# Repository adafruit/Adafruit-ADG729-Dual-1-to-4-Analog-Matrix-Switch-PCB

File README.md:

## Adafruit ADG729 Dual 1-to-4 Analog Matrix Switch PCB

<a href="http://www.adafruit.com/products/5932"><br/>
Click here to purchase one from the Adafruit shop</a>

PCB files for the Adafruit ADG729 Dual 1-to-4 Analog Matrix Switch. 

Format is EagleCAD schematic and board layout
* https://www.adafruit.com/product/5932

### Description

Analog switches are a solid state alternative to relays, when you want a smaller, lower-power technology that won't wear out mechanically. And, as the name implies, you can use the Adafruit ADG729 Dual 1-to-4 Analog Matrix Switches to connect between two sets of four analog signals, much like 8 mechanical switches. These chips tend to be tiny surface mount parts, so this breakout will let anyone use the ADG729 switch for signals up to 5V, without fiddly soldering.

The ADG729 uses I2C to select which of the 8 channels switches to turn on or off. Four channels connect to the DA analog pin, and the other four channels connect to the DB analog pin. Note that unlike digital switches and multiplexers, these are not 'input' and 'output' because the signal is bidirectional. You could have the DA or DB signal be an input to 4 outputs, or the 4 inputs to one output.

Also, the ADG729 isn't really a 'selecting multiplexer', its a matrix switch with 8 independent switches. That means that yes, you could treat it like an DP4T where you select which signal is routed to the D pin, you can also turn on multiple switches to 'merge' the signals together. If you want all 8 signals to be able to route to a single pin, check out the ADG728.

Unlike a relay or mechanical switch, analog switches don't wear out, and the switch time is near instant, about 100nS. The ADG729 chip also guarantees break-before-make so the deselected switches will open before selected switches close.

However, there's a few things to watch out for:

* The VIN power pin (the red wire if using a STEMMA QT cable) must as high as the highest analog voltages you want to switch. That means if the analog signals are no more than 5VDC, the V+ pin must be higher than 5V. You cannot power this pin with 3.3V and switch 5V signals.
* It cannot switch signals below ground. No negative voltages can be applied to the Switch or DA/DB pins!
* Analog switches are for signals, not power! Since this is not a mechanical switch, the signals pass through circuitry that is not designed to source or sink current. This is great for analog signal voltages, and is not good for providing more than a few mA of current.

In addition to the 8 switch S pins and the two D pins that can be switched to, there's also two I2C address pins so you can change the default address from 0x44 up to 0x47.

To get you going fast, we spun up a custom-made PCB in the STEMMA QT form factor, making it easy to interface with. The STEMMA QT connectors on either side are compatible with the SparkFun Qwiic I2C connectors. This allows you to make solderless connections between your development board and the ADG or to chain it with a wide range of other sensors and accessories using a compatible cable.

### License

Adafruit invests time and resources providing this open source design, please support Adafruit and open-source hardware by purchasing products from [Adafruit](https://www.adafruit.com)!

Designed by Limor Fried/Ladyada for Adafruit Industries.

Creative Commons Attribution/Share-Alike, all text above must be included in any redistribution. 
See license.txt for additional details.

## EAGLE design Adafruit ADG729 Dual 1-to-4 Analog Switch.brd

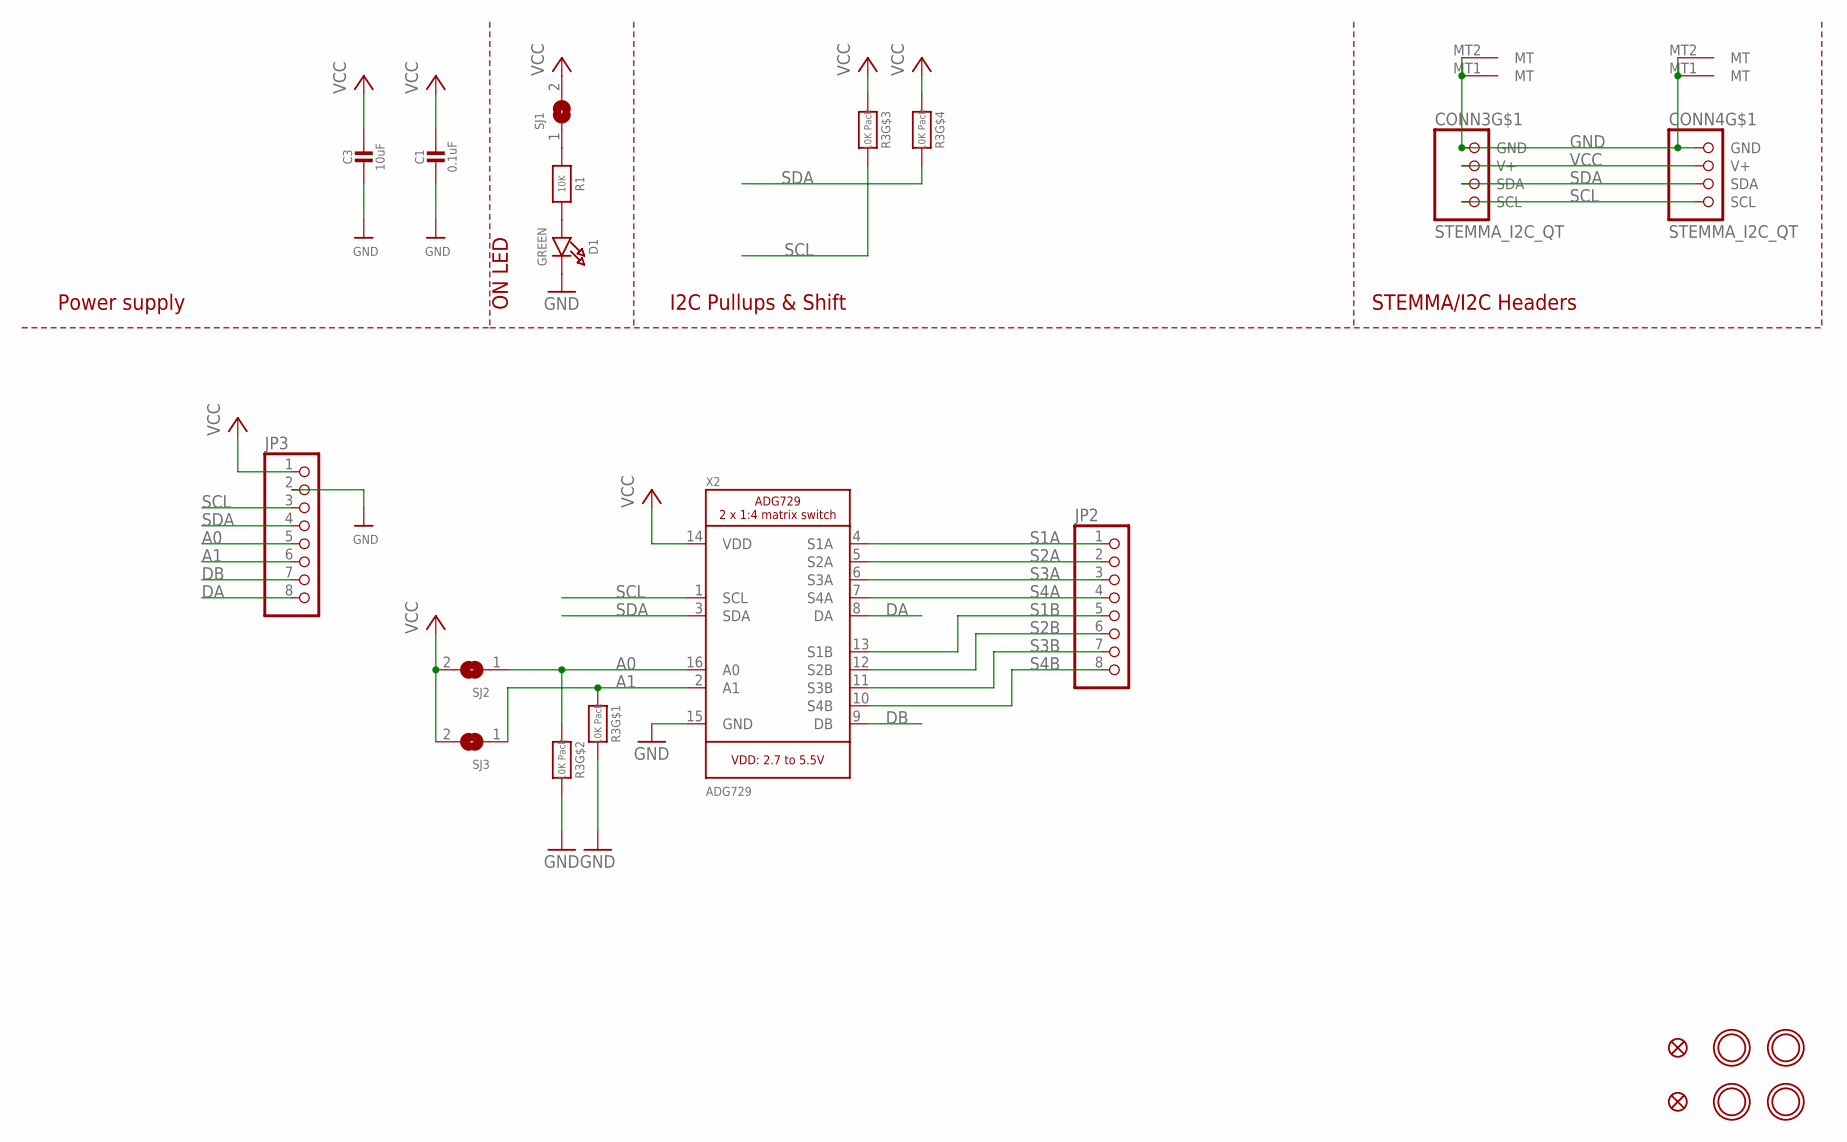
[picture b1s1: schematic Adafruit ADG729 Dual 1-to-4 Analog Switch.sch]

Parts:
C1: 0.1uF; 0603-NO
C3: 10uF; 0805-NO
CONN3, CONN4: STEMMA_I2C_QT; JST_SH4
D1: GREEN; CHIPLED_0603_NOOUTLINE
FID3, FID4: FIDUCIAL_1MM
JP2, JP3: HEADER-1X870MIL; 1X08_ROUND_70
R1: 10K; 0603-NO
R3: 10K Pack; RESPACK_4X0603
SJ1: SOLDERJUMPERCLOSED; SOLDERJUMPER_CLOSEDWIRE
SJ2, SJ3: SOLDERJUMPER; SOLDERJUMPER_ARROW_NOPASTE
U$1, U$17, U$19, U$21: MOUNTINGHOLE2.5; MOUNTINGHOLE_2.5_PLATED
X2: ADG729; TSSOP16

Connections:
A0: JP3.5, R3.2 (1), SJ2.1, X2.16 (A0)
A1: JP3.6, R3.1, SJ3.1, X2.2 (A1)
DA: JP3.8, X2.8 (DA)
DB: JP3.7, X2.9 (DB)
GND: C1.2, C3.2, CONN3.1 (GND), CONN3.MT1 (MT), CONN3.MT2 (MT), CONN4.1 (GND), CONN4.MT1 (MT), CONN4.MT2 (MT), D1.C, JP3.2, R3.7 (2), R3.8 (2), X2.15 (GND)
unnamed: D1.A, R1.2
unnamed: R1.1, SJ1.1
S1A: JP2.1, X2.4 (S1A)
S1B: JP2.5, X2.13 (S1B)
S2A: JP2.2, X2.5 (S2A)
S2B: JP2.6, X2.12 (S2B)
S3A: JP2.3, X2.6 (S3A)
S3B: JP2.7, X2.11 (S3B)
S4A: JP2.4, X2.7 (S4A)
S4B: JP2.8, X2.10 (S4B)
SCL: CONN3.4 (SCL), CONN4.4 (SCL), JP3.3, R3.6 (2), X2.1 (SCL)
SDA: CONN3.3 (SDA), CONN4.3 (SDA), JP3.4, R3.5 (2), X2.3 (SDA)
VCC: C1.1, C3.1, CONN3.2 (V+), CONN4.2 (V+), JP3.1, R3.3 (1), R3.4 (1), SJ1.2, SJ2.2, SJ3.2, X2.14 (VDD)

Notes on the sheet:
I2C Pullups & Shift
STEMMA/I2C Headers
ON LED
Power supply

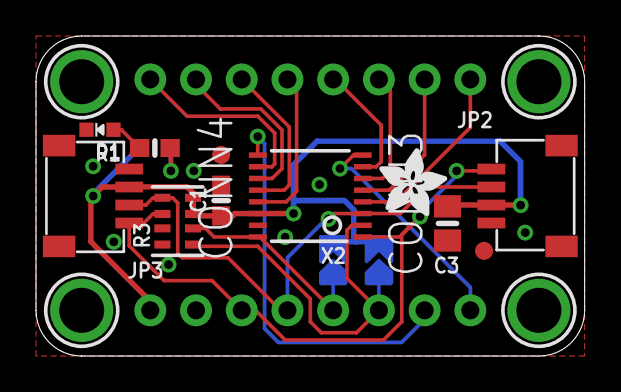
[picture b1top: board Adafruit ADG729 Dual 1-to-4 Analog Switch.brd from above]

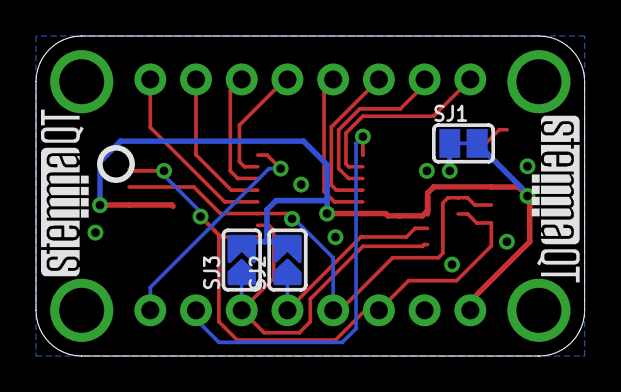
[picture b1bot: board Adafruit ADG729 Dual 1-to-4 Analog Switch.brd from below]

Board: 2 copper layers, 30.5 x 17.8 mm, 47 parts (12 on the bottom side), 18 nets.

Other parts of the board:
PLABEL0: PLABEL0
PLABEL1: PLABEL1
PLABEL2: PLABEL2
PLABEL3: PLABEL3
PLABEL4: PLABEL4
PLABEL5: PLABEL5
PLABEL6: PLABEL6
PLABEL7: PLABEL7
PLABEL8: PLABEL8
PLABEL9: PLABEL9
PLABEL10: PLABEL10
PLABEL11: PLABEL11
PLABEL12: PLABEL12
PLABEL13: PLABEL13
PLABEL14: PLABEL14
PLABEL15: PLABEL15
PLABEL16: PLABEL16
PLABEL17: PLABEL17
PLABEL18: PLABEL18
PLABEL19: PLABEL19
PLABEL20: PLABEL20
PLABEL21: PLABEL21
PLABEL22: PLABEL22
PLABEL23: PLABEL23
U$22: ADAFRUIT_3.5MM
U$25: PCBFEAT-REV-040
U$30, U$31: STEMMAQT

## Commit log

2024-04-10 cookiecutter

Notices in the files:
parts and their libraries:
microbuilder: This work is placed in the public domain, and may be freely used for commercial and non-commercial work with the following conditions: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
